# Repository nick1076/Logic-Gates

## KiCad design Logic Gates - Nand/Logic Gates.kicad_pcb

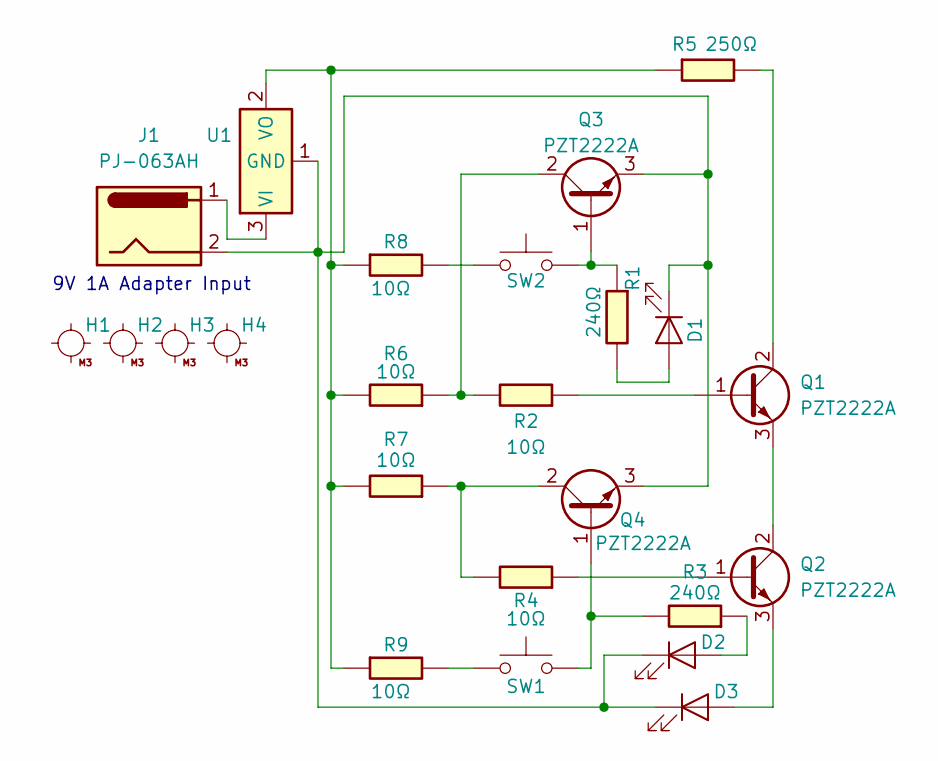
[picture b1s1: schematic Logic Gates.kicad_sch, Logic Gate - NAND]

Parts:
D1: 1206; LED_1206
D2, D3: LED 1206; LED_1206
H1, H2, H3, H4: MountingHole_M3
J1: PJ-063AH; BarrelJack_CUI_PJ-063AH_Horizontal
Q1, Q2, Q3, Q4: PZT2222A; SOT-223-3_TabPin2
R1, R3: 240Ω; R_1206
R2, R4, R6, R7, R8, R9: 10Ω; R_1206
R5: 250Ω; R_1206
SW1, SW2: SMD Momentary Button; Button_CnK_PTS636.0_6x3.5mm
U1: Linear Regulator SMD; SOT-223-3_TabPin2

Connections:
unnamed: D1.2 (A), R1.1
unnamed: D1.1 (K), D2.1 (K), D3.1 (K), J1.2, Q3.3 (E), Q4.3 (E), U1.1 (GND)
unnamed: D2.2 (A), R3.2
unnamed: D3.2 (A), Q2.3 (E)
unnamed: Q1.1 (B), R2.2
unnamed: Q1.2 (C), R5.1
unnamed: Q1.3 (E), Q2.2 (C)
unnamed: Q2.1 (B), R4.2
unnamed: Q3.1 (B), R1.2, SW2.2
unnamed: Q3.2 (C), R2.1, R6.2
unnamed: Q4.1 (B), R3.1, SW1.2
unnamed: Q4.2 (C), R4.1, R7.2
unnamed: R8.1, SW2.1
unnamed: R9.1, SW1.1
unnamed: J1.1, U1.3 (VI)
unnamed: R5.2, R6.1, R7.1, R8.2, R9.2, U1.2 (VO)

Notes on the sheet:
9V 1A Adapter Input

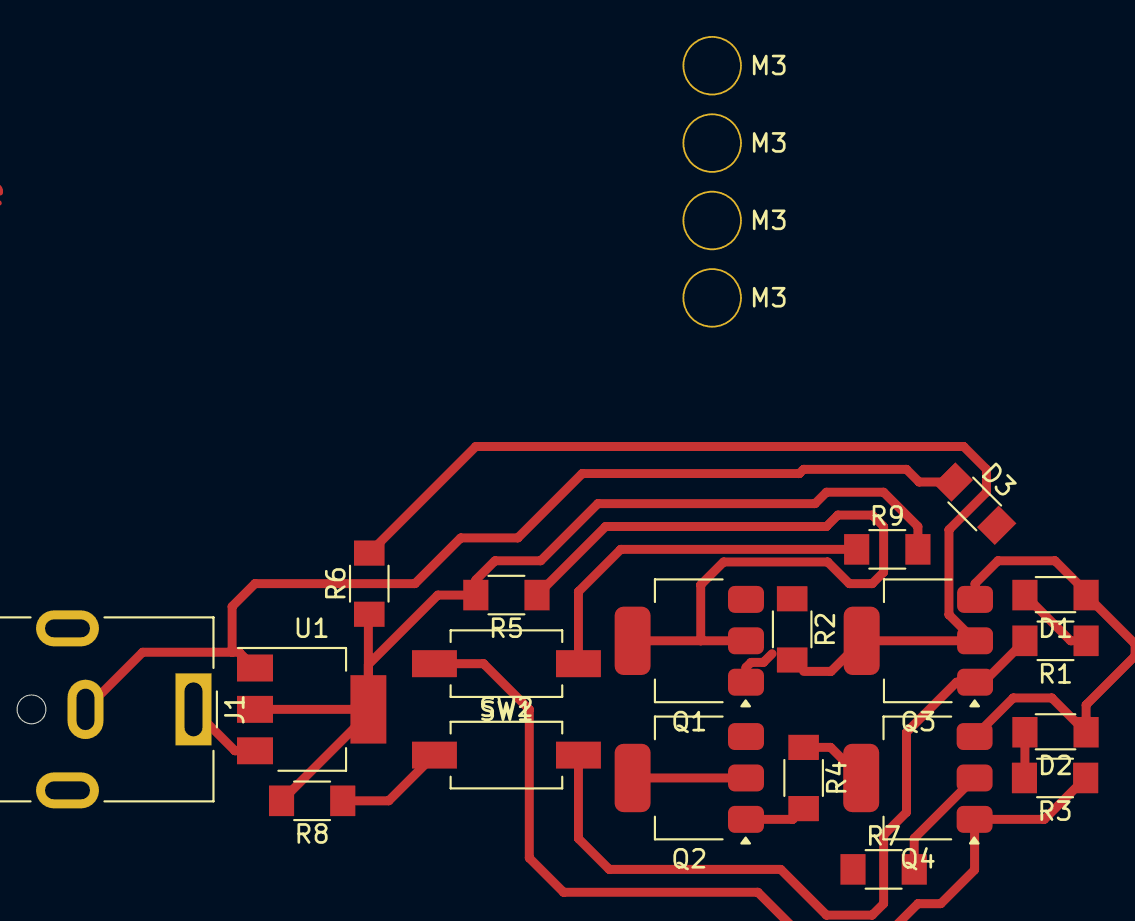
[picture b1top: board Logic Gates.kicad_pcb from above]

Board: 2 copper layers, 24 parts (0 on the bottom side), 16 nets.

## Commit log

2024-06-21 AND gate creation (Schematic, PCB, SVGs)
    Initial push including fully developed AND gate PCB
2024-06-21 SVG Updates
2024-06-24 NAND addition
